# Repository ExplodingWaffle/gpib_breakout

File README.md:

# gpib_breakout
 Breakout PCB for GPIB (IEEE-488) connector.

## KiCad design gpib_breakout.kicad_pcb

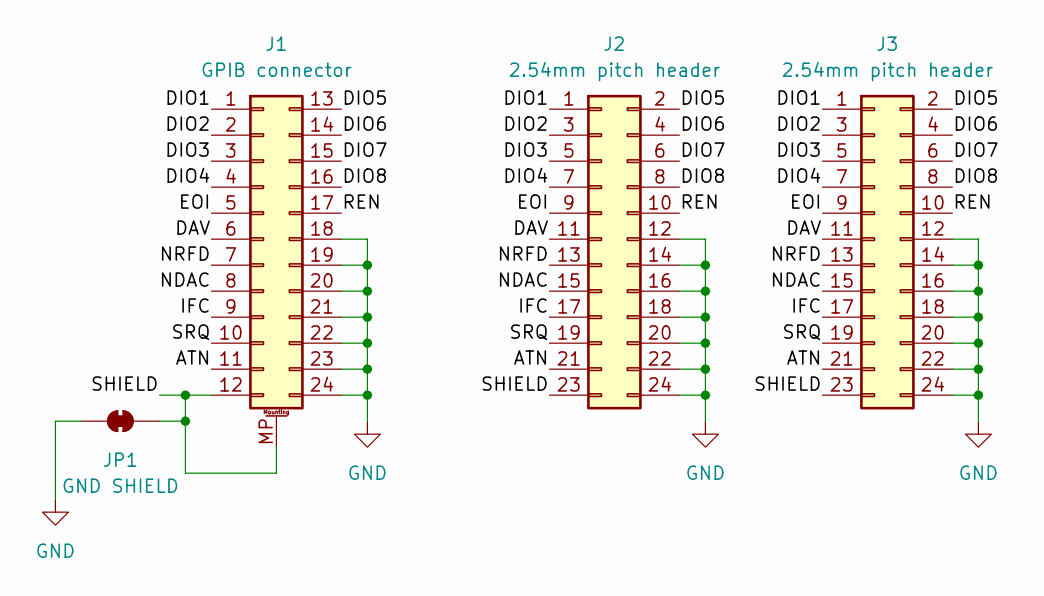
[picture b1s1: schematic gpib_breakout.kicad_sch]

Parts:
J1: GPIB connector; GPIB_Conn
J2, J3: 2.54mm pitch header; PinHeader_2x12_P2.54mm_Vertical
JP1: GND SHIELD; SolderJumper-2_P1.3mm_Bridged_RoundedPad1.0x1.5mm

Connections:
/ATN: J1.11, J2.21, J3.21
/DAV: J1.6, J2.11, J3.11
/DIO1: J1.1, J2.1, J3.1
/DIO2: J1.2, J2.3, J3.3
/DIO3: J1.3, J2.5, J3.5
/DIO4: J1.4, J2.7, J3.7
/DIO5: J1.13, J2.2, J3.2
/DIO6: J1.14, J2.4, J3.4
/DIO7: J1.15, J2.6, J3.6
/DIO8: J1.16, J2.8, J3.8
/EOI: J1.5, J2.9, J3.9
/IFC: J1.9, J2.17, J3.17
/NDAC: J1.8, J2.15, J3.15
/NRFD: J1.7, J2.13, J3.13
/REN: J1.17, J2.10, J3.10
/SHIELD: J1.12, J1.MP (MountPin), J2.23, J3.23, JP1.2 (B)
/SRQ: J1.10, J2.19, J3.19
GND: J1.18, J1.19, J1.20, J1.21, J1.22, J1.23, J1.24, J2.12, J2.14, J2.16, J2.18, J2.20, J2.22, J2.24, J3.12, J3.14, J3.16, J3.18, J3.20, J3.22, J3.24, JP1.1 (A)

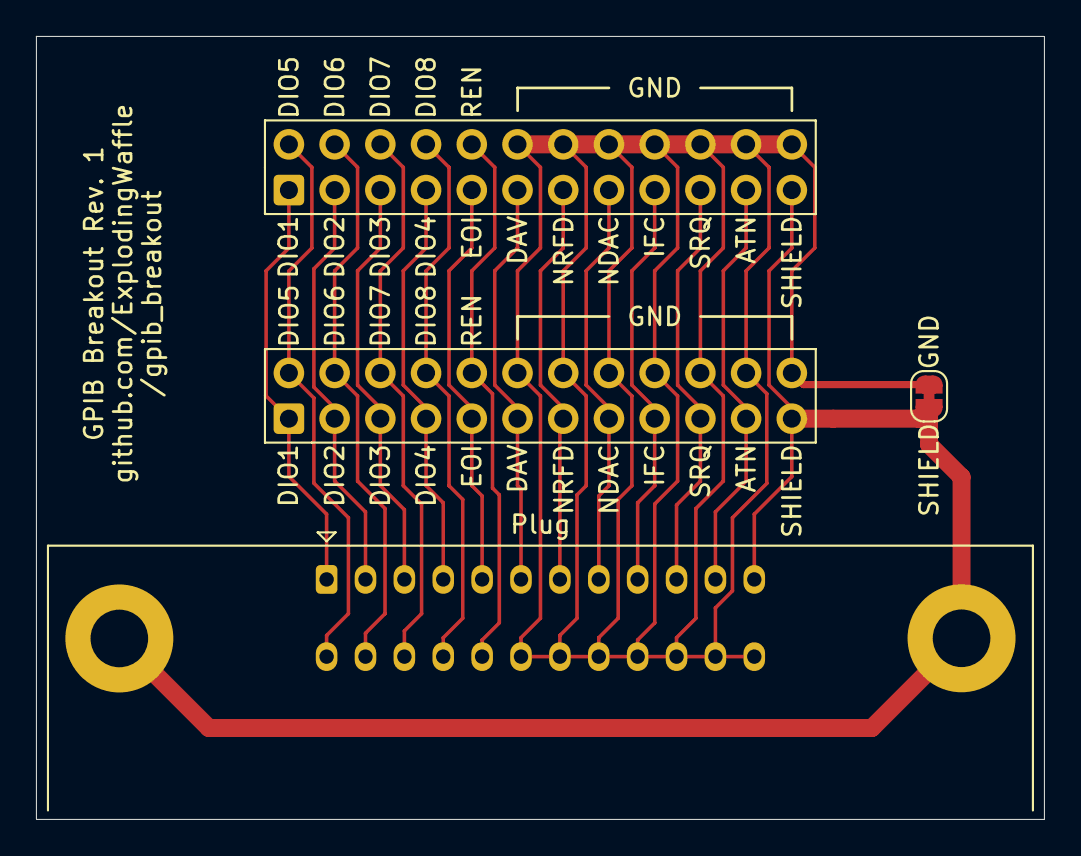
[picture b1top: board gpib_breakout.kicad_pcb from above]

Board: 2 copper layers, 56.0 x 43.5 mm, 4 parts (0 on the bottom side), 18 nets.

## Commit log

2025-03-15 Create main.yml for GHA
